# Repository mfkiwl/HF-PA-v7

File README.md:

### HF-PA-v3

VU3CER's Robust `Class-C / Class-D HF PA` for https://github.com/kholia/Easy-Digital-Beacons-v1
project for 40-20-17-15-12-10m bands - powered by RD16HHF1 RF MOSFET.

This design aspires to be the standard mW-to-QRP-Gallon HF PA in the ~1100 INR
(15 USD) design space.

If you are looking for a ~600 INR IRF510 design, please check out the
https://github.com/kholia/HF-PA-v5 project.

Design Constraints:

- PCB is to be homebrewed.

- PCB is single-sided - only one layer (side) is available for routing work.

- The "finals" MOSFET needs to be on an edge to allow usage of heatsinks.

- Typical external linears (e.g. `PA150 HF Linear Amp`) need 2W minimum to
  function. So we need a minimum of 2W of RF output from our design - even at
  28 MHz (10m).

- Minimal part count is strongly preferred. Low cost, and ease of availability
  are strong driving and deciding factors.

- Reproducibility is a MUST! We focus a lot on this aspect by documenting each,
  and every detail possible.

- Repairability in the field is a MUST!

  Dhiru's finding: Repairing homebrewed PCBs is so much easier, and fun than
  reworking commercial `lead-free` PTH PCBs.

- No moving mechanical parts are allowed in the design - this rules out usage
  of (failure-prone) active cooling options like fans.

Input: Few milliwatts is fine. Note: Si5351's output is around 8-10mW.

Output: To be done.

Robustness check: The PA works fine with 100% duty cycle for more than 8 hours!
In real-life, WSPR defaults to using ~2-minute TX intervals every 10 minutes.
FT8 is naturally gapped every ~15 seconds, and so on. We have also run FT8 on
this HF PA for more than a day at a time. The whole `HF PA v3` system is
thermally super stable.

Note 1: The output power is software controllable (via `PWM grounding`) for
flexibility.

Note 2: The idea behind making these (and my other) design notes publicly
available is to deliver REPRODUCIBLE, flexible, home-brewable, standardized,
reasonable, and cost-effective solutions for some common problems. I include
many references, simulations, and notes in my projects to enable you to do your
own (better) designs - do share them ;)

(Image Credit: `Wanting` book by Luke Burgis)

Note 3: All screenshots are clickable and zoomable.

Please see the older https://github.com/kholia/HF-PA-v2 project for the
power-supply (over-current protected)i design.

Schematic:

PCB rendering:

LPF rendering:

#### PA tuning process

- Remove the MOSFET from the TO-220 socket.

- Set the gate bias to a minimum (~0v).

- Enable PTT.

- Increase gate bias so that Idq (drain current) is in the range of 250mA to
  600mA for RD16HHF1.

- Turn off PTT.

- Connect the RD16HHF1 MOSFET back, enable PTT, enable RF input, and measure RF
  output.

Reference: http://www.carnut.info/WSPR_Tx/WSPR_Tx.htm

#### PA BOM

- 1 x SN74ACT04N (TI) - 65 INR

- 1 x RD16HHF1 - ~500 INR

  - Beware of fakes. Ensure proper sourcing (trusted supply chain, etc) to get
    genuine parts.

- 1 x IRF4905 OR IRF9540 P-Channel TO-220 MOSFET - 50 INR

- 5k Preset (Potentiometer) RM-065 - 15 to 20 INR

- 4 x 10k Ohm - 0.25W Metal Film Resistor - 10 INR

- 1 x 100k Ohm - 0.25W Metal Film Resistor - 5 INR

- 1 x 10 Ohm - 0.25W Metal Film Resistor - 5 INR

- 1 x 3.3k Ohm - 0.25W Metal Film Resistor - 5 INR

- 1 x 4.7k Ohm - 0.25W Metal Film Resistor - 5 INR

- A very large heat sink - 50 to 200 INR - larger heatsink is better!

- 1 x 7806 (TO-220 package from CDIL / ST) Voltage Regulator - 20 INR

- 2 x SMA connectors (PCB mount) - 50 INR

- 1 x 2N7000 TO-92 MOSFET - 10 INR

- 5 x 100nF (104) 50v Ceramic Capacitor - 15 INR

- 2 x 100nF (104) 100v Ceramic Capacitor - 15 INR

- 1 x 22uF 25v Electrolytic Capacitor - 5 INR

- 1 x FT50-43 (Black Toroid) - <= 30 INR

  Note: A bigger "FT68-43" toroid might be better at higher power levels.

- Misc: Relimate Connectors, Copper Clad PCB, Various Consumables (~100 INR)

- Tools: LCR-T4 Meter (for measuring things), RF Power Meter

- PA Total Cost: ~1100 INR

#### Power Supply BOM

See https://github.com/kholia/HF-PA-v2.

#### BOM + Equipment Sources

- https://www.semikart.com/ (IRF510, NP0 LPF caps - Kemet and others)

  - Multicomp Pro 100v C0G caps from Element14 are recommended

- https://www.semikart.com/search/SN74ACT04N

- https://www.electronicscomp.com/

  - IRF510 (Vishay), regular caps, ST voltage regulators

- https://www.electroncomponents.com/ (transistors, connectors, consumables, misc)

- https://www.sunrom.com/ (regular ceramic caps, SMA connectors, SIP socket strip)

- https://projectpoint.in/

  - Transistors, regular caps, voltage regulators, pots / trimmers, MFR resistors, misc

  - 2-Pin High Quality Relimate Connectors (all those 2-pin headers are actually Relimate Connectors)

  - Copper Magnetic Winding Wire

  - 3-Pin Relimate Cable Female to Female (High Quality 2500mA) - 'TO-220 socket'

- Semikart - Toroids

- https://www.techtonics.in - 300W DC-DC Buck Converter Constant Current Module

- eBay (`gr_makis`) - Toroids, RD16HHF1 MOSFETs

- https://www.sdr-kits.net/ - RD16HHF1 MOSFETs

- https://www.ktron.in/ (SMA connectors, excellent prices for many things)

- [LCR-T4 LCR Meter](https://www.techtonics.in/lcr-t4-12864-lcd-graphical-transistor-tester-resistance-capacitance-esr-scr-meter)

- [AVOID] https://www.fabtolab.com/78l05-voltage-regulator (https://www.ventor.co.in also works)

- https://robu.in/ (voltage boost module)

- https://indialocalshop.com/ - misc. hardware

- http://www.bhadraenclosures.com/ - excellent protected enclosures

Note for international buyers: The BOM can be carefully sourced via Mouser and DigiKey.

#### Notes

The included LPF module DOES NOT require the `same-side soldering` hack.

#### Tips

MOSFETs are sensitive with regards to ESD and high soldering temperatures. Use
best practices when dealing with MOSFETs and perhaps always ;)

By using these `TO-220 Sockets`, we can easily support any MOSFET pinout. This
technique allows usage of `off-pcb` heat sinks with a lot of flexibility. It
also avoids common ESD + MOSFET problems as well. The gate bias can be easily
checked by safely removing the MOSFET from the TO-220 socket. Also, this socket
idea allows us to safely eliminate the LDO from the design.

`SN74ACT04N` can be driven at 6v - this is the secret LU2HES sauce! RF input
drive strength matters the most.

A burnt 78(L)05 regulator can easily eat up 4-5W of power by itself. If there
is no RF output but power is being consumed then check your linear regulator.

#### References

See [References.md](./References.md).

#### Credits

This design uses ideas from VU2ASH, HAMBREWERS, QRP Labs, Tom (AK2B), VK3PE,
and G6LBQ.

Also see https://github.com/kholia/HF-PA-v5#credits.

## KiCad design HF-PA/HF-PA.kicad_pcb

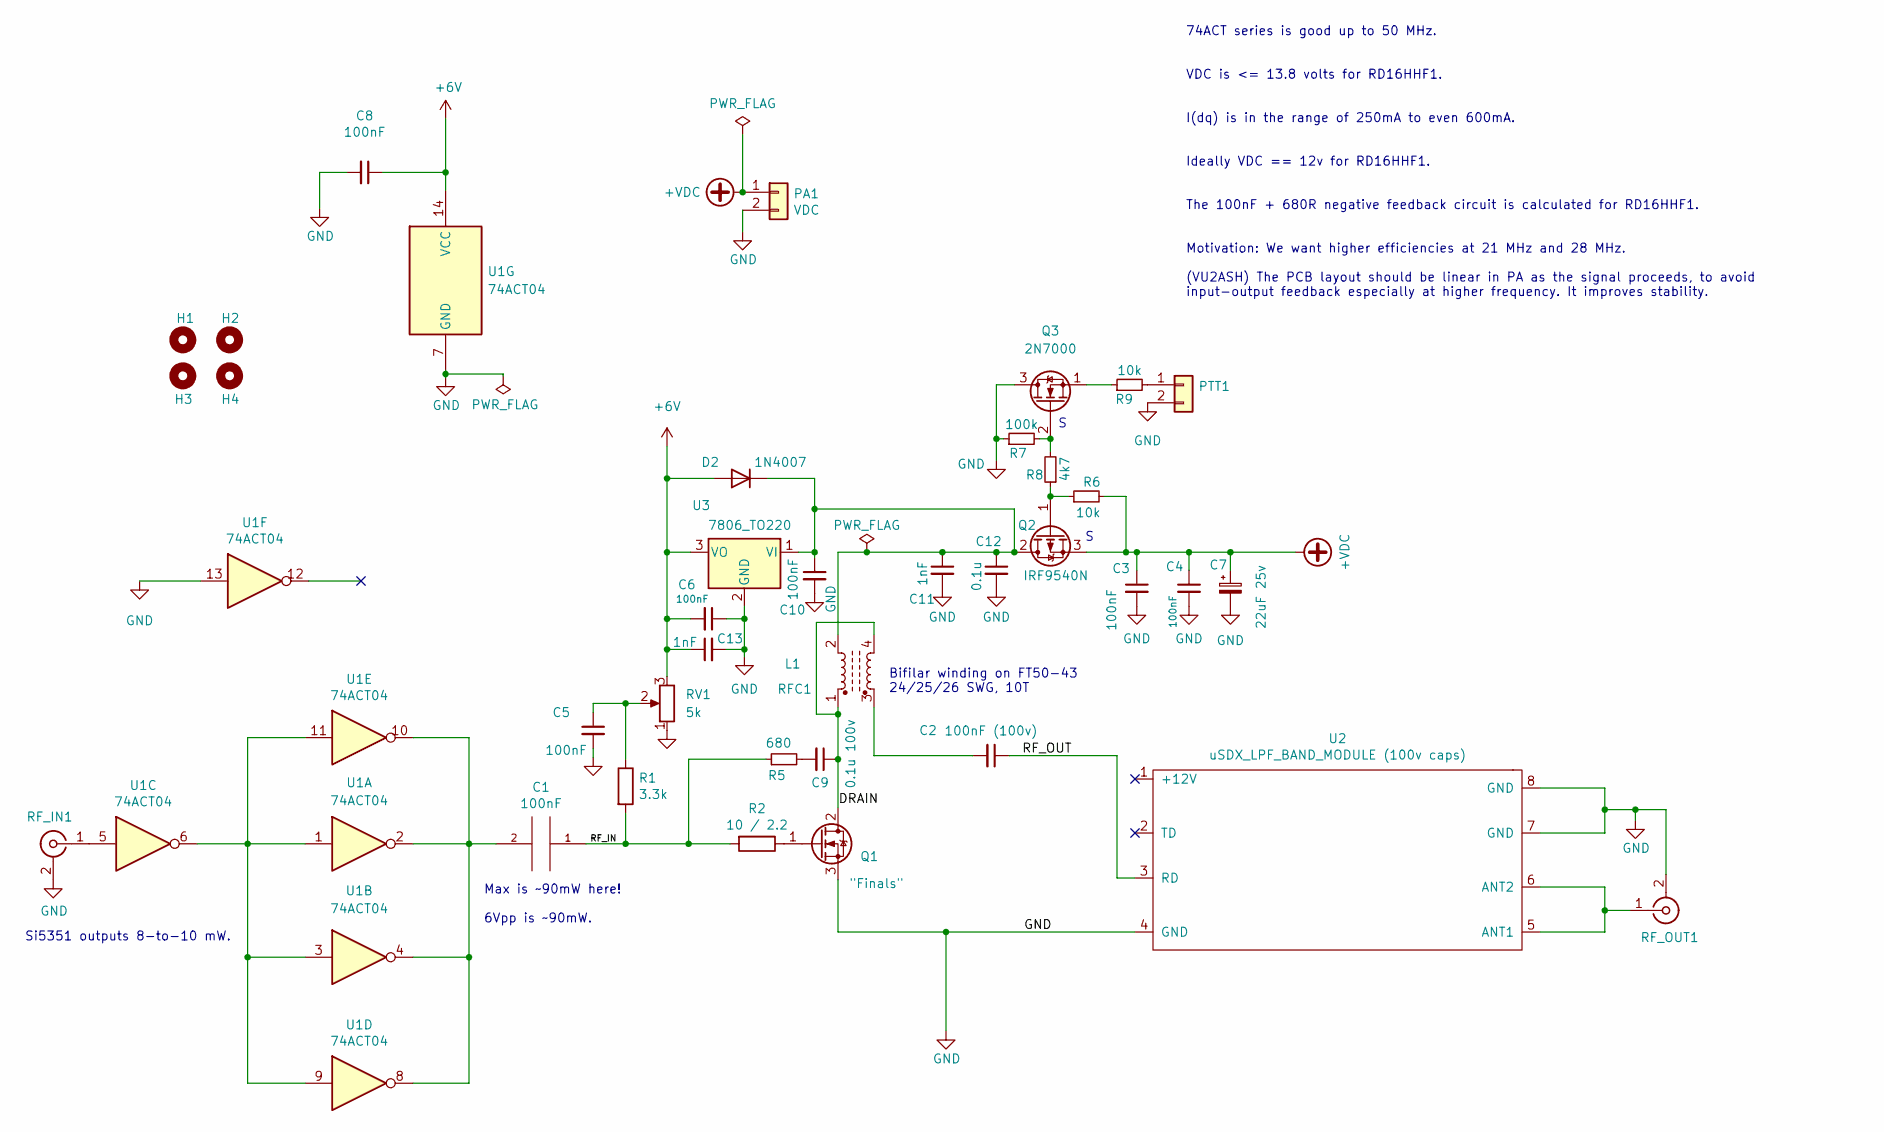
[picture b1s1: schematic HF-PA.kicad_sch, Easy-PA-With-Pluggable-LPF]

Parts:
C1, C3, C4, C5, C6, C8, C10: 100nF; C_Disc_D4.3mm_W1.9mm_P5.00mm
C2: 100nF (100v); C_Disc_D4.3mm_W1.9mm_P5.00mm
C7: 22uF 25v; CP_Radial_D5.0mm_P2.50mm
C9: 0.1u 100v; C_Disc_D4.3mm_W1.9mm_P5.00mm
C11, C13: 1nF; C_Disc_D4.3mm_W1.9mm_P5.00mm
C12: 0.1u; C_Disc_D4.3mm_W1.9mm_P5.00mm
D2: 1N4007; D_DO-41_SOD81_P2.54mm_Vertical_AnodeUp
H1, H2, H3, H4: MountingHole; MountingHole_2.2mm_M2
L1: RFC1; FT50-43 Transformer
PA1: VDC; PinHeader_1x02_P2.54mm_Vertical
PTT1: PTT; PinHeader_1x02_P2.54mm_Vertical
Q1: "Finals"; TO-220-3_Vertical
Q2: IRF9540N; TO-220-3_Vertical
Q3: 2N7000; PinSocket_1x03_P2.54mm_Vertical
R1: 3.3k; R_Axial_DIN0207_L6.3mm_D2.5mm_P2.54mm_Vertical
R2: 10 / 2.2; R_Axial_DIN0207_L6.3mm_D2.5mm_P2.54mm_Vertical
R5: 680; R_Axial_DIN0207_L6.3mm_D2.5mm_P2.54mm_Vertical
R6, R9: 10k; R_Axial_DIN0207_L6.3mm_D2.5mm_P2.54mm_Vertical
R7: 100k; R_Axial_DIN0207_L6.3mm_D2.5mm_P2.54mm_Vertical
R8: 4k7; R_Axial_DIN0207_L6.3mm_D2.5mm_P2.54mm_Vertical
RF_IN1: Conn_Coaxial; SMA_Amphenol_901-144_Vertical
RF_OUT1: Conn_Coaxial; SMA_Amphenol_901-144_Vertical
RV1: 5k; Potentiometer_Runtron_RM-065_Vertical_
U1: 74ACT04; DIP-14_W7.62mm_LongPads
U2: uSDX_LPF_BAND_MODULE (100v caps); uSDX_LPF_Band_Module
U3: 7806_TO220; TO-220-3_Vertical

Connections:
+6V: C6.2, C8.1, C13.1, D2.2 (A), RV1.3, U1.14 (VCC), U3.3 (VO)
+VDC: C3.1, C4.1, C7.1, PA1.1, Q2.3 (S), R6.2
/DRAIN: C9.1, L1.1, L1.4, Q1.2 (D)
/RF_IN: C1.1, R1.2, R2.2, R5.1
/RF_OUT: C2.1, U2.3 (RD)
GND: C3.2, C4.2, C5.2, C6.1, C7.2, C8.2, C10.2, C11.2, C12.2, C13.2, PA1.2, PTT1.2, Q1.3 (S), Q3.3 (D), R7.1, RF_IN1.2 (Ext), RF_OUT1.2 (Ext), RV1.1, U1.7 (GND), U1.13, U2.4 (GND), U2.7 (GND), U2.8 (GND), U3.2 (GND)
unnamed: C1.2, U1.2, U1.4, U1.8, U1.10
unnamed: C2.2, L1.3
unnamed: C5.1, R1.1, RV1.2
unnamed: C9.2, R5.2
unnamed: C10.1, C11.1, C12.1, D2.1 (K), L1.2, Q2.2 (D), U3.1 (VI)
unnamed: PTT1.1, R9.2
unnamed: Q1.1 (G), R2.1
unnamed: Q2.1 (G), R6.1, R8.1
unnamed: Q3.1 (S), R9.1
unnamed: Q3.2 (G), R7.2, R8.2
unnamed: RF_IN1.1 (In), U1.5
unnamed: RF_OUT1.1 (In), U2.5 (ANT1), U2.6 (ANT2)
unnamed: U1.1, U1.3, U1.6, U1.9, U1.11

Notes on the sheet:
74ACT series is good up to 50 MHz. VDC is <= 13.8 volts for RD16HHF1. I(dq) is in the range of 250mA to even 600mA. Ideally VDC == 12v for RD16HHF1. The 100nF + 680R negative feedback circuit is calculated for RD16HHF1. Motivation: We want higher efficiencies at 21 MHz and 28 MHz. (VU2ASH) The PCB 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
Max is ~90mW here! 6Vpp is ~90mW.
Si5351 outputs 8-to-10 mW.
Bifilar winding on FT50-43 24/25/26 SWG, 10T

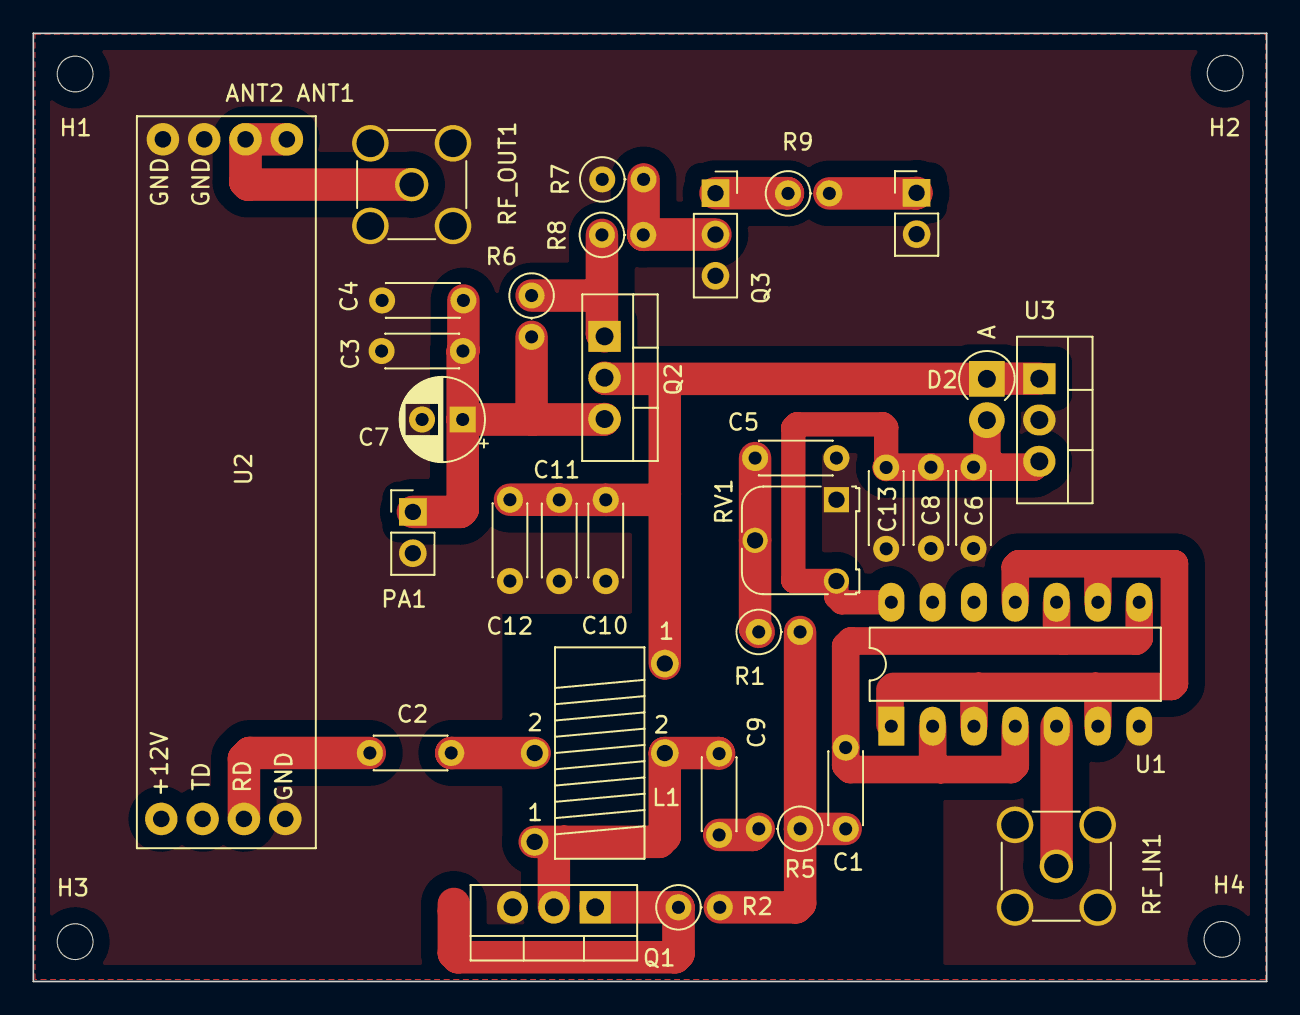
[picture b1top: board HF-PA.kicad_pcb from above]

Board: 2 copper layers, 75.8 x 58.3 mm, 37 parts (0 on the bottom side), 19 nets.

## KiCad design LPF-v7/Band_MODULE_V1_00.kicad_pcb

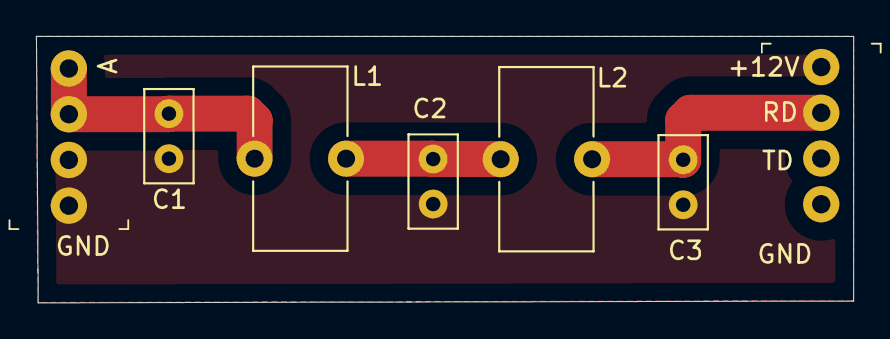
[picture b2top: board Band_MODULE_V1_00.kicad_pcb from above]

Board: 2 copper layers, 45.4 x 14.8 mm, 7 parts (0 on the bottom side), 4 nets.

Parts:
C1, C3: 100pF; C_Disc_D5.0mm_W2.5mm_P2.50mm
C2: 180pF; C_Disc_D5.0mm_W2.5mm_P2.50mm
J1: Antenna; PinHeader_1x4_P2.54mm_Drill1.02mm
J2: input; PinHeader_1x4_P2.54mm_Drill1.02mm
L1, L2: 330nH; L_Toroid_Vertical_L10.0mm_W5.0mm_P5.08mm

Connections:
GNDPWR: C1.2, C2.2, C3.2, J1.1, J1.2, J2.1
unnamed: C1.1, J1.3, J1.4, L1.1
unnamed: C2.1, L1.2, L2.1
unnamed: C3.1, J2.2, L2.2
